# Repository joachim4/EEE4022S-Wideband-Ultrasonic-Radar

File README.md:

# EEE4022S-Wideband-Ultrasonic-Radar
This repository contains the files necessary for carrying out the design and implementation of a well packaged Continuous Wave (CW) radar demonstrator system for estimating the speed of moving objects.

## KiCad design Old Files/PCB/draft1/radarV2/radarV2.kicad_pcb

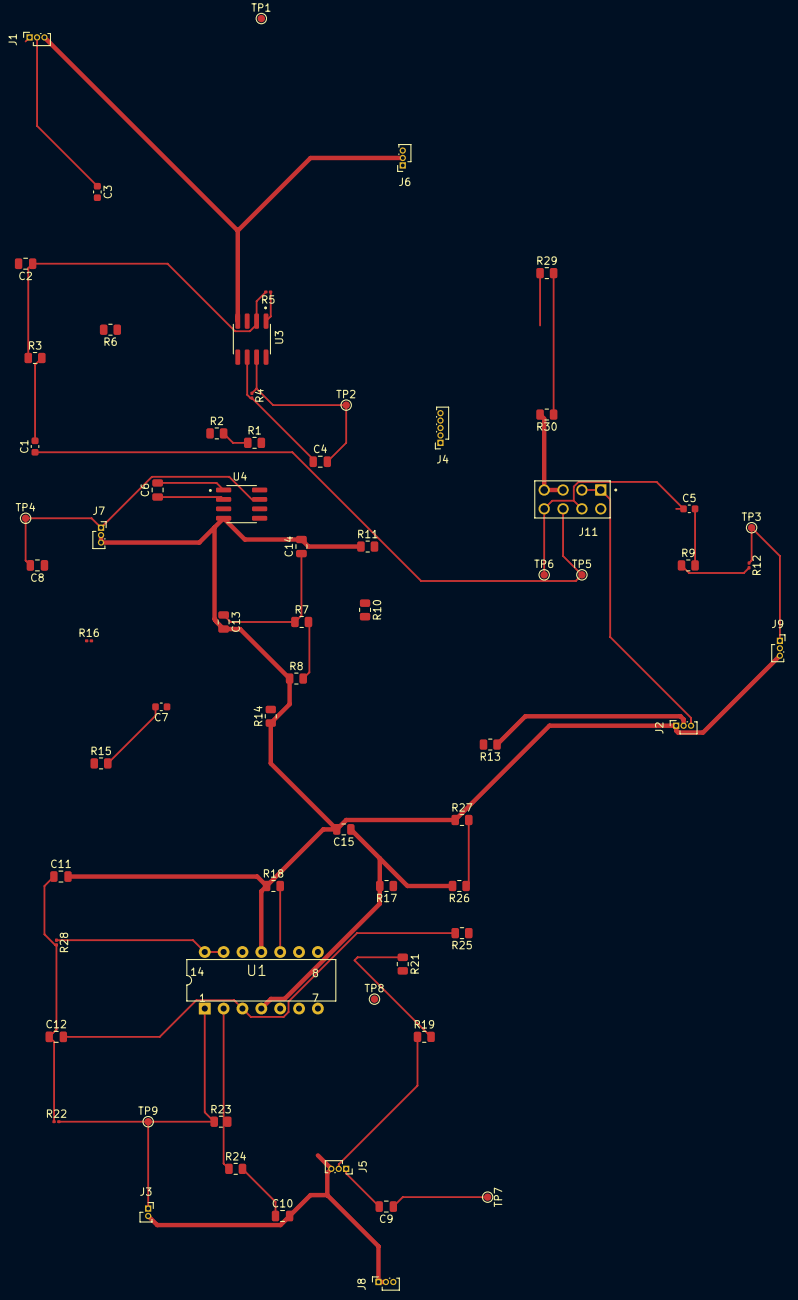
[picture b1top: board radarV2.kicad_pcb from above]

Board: 2 copper layers, 66 parts (0 on the bottom side), 38 nets.

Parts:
C1, C3, C5, C7: 6.8n; C_0603_1608Metric
C2, C4, C6, C8: 22p; C_0805_2012Metric
C9, C10: 10u; C_0805_2012Metric
C11, C12: 2.2n; C_0805_2012Metric
C13, C14, C15: 0.1u; C_0805_2012Metric
J1, J2, J5, J6, J7, J8, J9: Conn_01x03_Socket; PinSocket_1x03_P1.00mm_Vertical
J3: Conn_01x02_Socket; PinSocket_1x02_P1.00mm_Vertical
J4: Conn_01x05_Socket; PinSocket_1x05_P1.00mm_Vertical
J11: PH2-08-UA; ADAM_PH2-08-UA
R1, R2, R7, R8, R10, R11, R13, R14, R17, R18: 10k; R_0805_2012Metric
R3, R6, R9, R15, R26, R27: 1.2k; R_0805_2012Metric
R4, R5, R12, R16: 120k; R_0201_0603Metric
R19: 10; R_0805_2012Metric
R21: 1k; R_0805_2012Metric
R22, R28: 1.8k; R_0201_0603Metric
R23: 20k; R_0805_2012Metric
R24: 11k; R_0805_2012Metric
R25: 3k; R_0805_2012Metric
R29: 240; R_0805_2012Metric
R30: 390; R_0805_2012Metric
TP1, TP2, TP3, TP4, TP5, TP6, TP7, TP8, TP9: TestPoint; TestPoint_Pad_D1.0mm
U1: MC33079; DIL14
U3, U4: TL082; SOIC127P600X175-8N

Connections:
+3.3V: C13.1, C14.1, J2.2, J4.4, R1.2, R7.1, R10.2, R13.1, R29.1, U3.8 (V+), U4.8 (V+)
+12V: C15.1, J4.1, J4.3, R17.2, R26.2, U1.4 (V+)
GND: C10.2, C11.2, C13.2, C14.2, C15.2, J1.3, J2.1, J3.2, J4.2, J5.3, J6.2, J6.3, J7.2, J7.3, J8.1, J8.2, J9.3, J11.5, J11.7, R2.1, R8.1, R11.1, R14.1, R18.1, R27.1, R30.2, U1.5 (+), U1.6 (-), U1.7, U1.11 (V-), U3.4 (V-), U4.4 (V-)
unnamed: C1.2, R3.2
unnamed: C3.2, R6.2
unnamed: C5.2, R9.2
unnamed: C7.2, R15.2
unnamed: C10.1, R24.2
unnamed: C11.1, C12.1, R22.1, R28.2
unnamed: C2.2, J1.1, R5.1, TP1.1, U3.1
unnamed: C3.1, J1.2
unnamed: J4.5, R29.2, R30.1
unnamed: C9.2, J5.1
unnamed: J5.2, R19.1
unnamed: C9.1, J8.3, TP7.1
unnamed: C6.2, J9.1, R12.1, TP3.1, U4.1
unnamed: C7.1, J9.2
unnamed: R25.1, R26.1, R27.2
unnamed: C12.2, R25.2, U1.3 (+)
unnamed: R23.2, R24.1, U1.2 (-)
unnamed: R17.1, R18.2, U1.10 (+)
unnamed: R19.2, R21.1, U1.9 (-)
unnamed: R21.2, TP8.1, U1.8, U1.12 (+)
unnamed: R28.1, U1.13 (-), U1.14
unnamed: R1.1, R2.2, U3.3 (+)
unnamed: C2.1, R3.1, R5.2, U3.2 (-)
unnamed: R7.2, R8.2, U3.5 (+)
unnamed: C4.1, R4.2, R6.1, U3.6 (-)
unnamed: R10.1, R11.2, U4.3 (+)
unnamed: C6.1, R9.1, R12.2, U4.2 (-)
unnamed: R13.2, R14.2, U4.5 (+)
unnamed: C8.1, R15.1, R16.2, U4.6 (-)
RxIn: J2.3, J11.1, J11.3
RxIn1: C1.1, J11.2, J11.6, TP5.1
RxIn2: C5.1, J11.4, J11.8, TP6.1
RxOut1: C4.2, J6.1, R4.1, TP2.1, U3.7
RxOut2: C8.2, J7.1, R16.1, TP4.1, U4.7
TxOut: J3.1, R22.2, R23.1, TP9.1, U1.1

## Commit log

2024-09-21 Added PCB Files
2024-09-21 Added simulation files
2024-10-23 Added new PCB files
2024-10-23 Added updated Matlab processing files
